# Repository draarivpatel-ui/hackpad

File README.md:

# AarivPad - My 3x3 Mechanical Macropad + EC11 Rotary Encoder + OLED

**Try the Live Interactive 3D Hardware Workbench & KMK Simulator:** [https://aariv.me/hackpad/](https://aariv.me/hackpad/)

I designed and built **AarivPad** for the Hack Club Stardance **Hackpad** mission. It is a custom 3x3 mechanical macropad powered by a **Seeed Studio XIAO RP2040**, an **Alps EC11 rotary encoder** with push-button switch, a **0.91" 128x32 SSD1306 I2C OLED status display**, and four **SK6812 MINI-E reverse-mount addressable RGB underglow LEDs**.

Alongside the complete KiCad 8 schematic, 2-layer routed PCB, JLCPCB Gerber archive, parametric OpenSCAD enclosure STLs, and CircuitPython KMK firmware, I also built an interactive browser workbench at [https://aariv.me/hackpad/](https://aariv.me/hackpad/) so you can test all 9 keys across all 3 macro layers, spin the EC11 encoder, inspect the 2-layer copper traces, and orbit the exploded 3D CAD assembly directly in your browser.

## Why I Built This

Whenever I am working across terminal Git sessions, KiCad PCB layout, and media playback, I constantly find myself reaching for awkward multi-finger keyboard chords (`git status`, `git diff --stat`, `git log --oneline -n 15`, switching tmux panes, or toggling KiCad copper layers and track widths).

I wanted a compact desk companion that sits right next to my mouse and gives me:
1. **Nine tactile mechanical switches** arranged in a standard `19.05mm` (`0.75"`) 3x3 grid for single-press macros.
2. **A physical EC11 rotary encoder** at the top-right corner so I can scrub timelines, adjust volume, or zoom in and out of KiCad/CAD viewports with tactile detents.
3. **A crisp 128x32 SSD1306 OLED screen** at the top-left so I never have to guess which macro layer (`L0: GIT/DEV`, `L1: MEDIA/RGB`, or `L2: KICAD/CAD`) is currently active.

## Features & How It Works Under the Hood

### 1. 3x3 Anti-Ghosting Switch Matrix + Peripherals on 11 GPIOs
Because the **Seeed Studio XIAO RP2040** exposes exactly 11 user GPIO pins (`D0` through `D10`), fitting 9 switches, a quadrature rotary encoder + push button, an I2C OLED display, and an addressable RGB LED chain required careful pin budgeting:
- **Columns (`COL0..COL2`)**: Wired to `D0` (`GPIO26`), `D1` (`GPIO27`), and `D2` (`GPIO28`).
- **Rows (`ROW0..ROW2`)**: Wired to `D3` (`GPIO29`), `D6` (`GPIO0`), and `D7` (`GPIO1`) through nine `1N4148W` SOD-123 switching diodes (`D1..D9`) oriented `COL2ROW` so pressing any combination of keys simultaneously never causes ghosting.
- **Hardware I2C0 (`SDA` / `SCL`)**: Reserved `D4` (`GPIO6`) and `D5` (`GPIO7`) for the 0.91" 128x32 SSD1306 OLED display at address `0x3C`.
- **EC11 Encoder & Underglow Chain**: Quadrature channels `ENC_A` and `ENC_B` connect to `D8` (`GPIO2`) and `D9` (`GPIO4`), while `D10` (`GPIO3`) handles the encoder push switch (`ENC_SW`) and drives the 4-pixel `SK6812 MINI-E` RGB underglow chain.

### 2. Three-Layer KMK Firmware (`firmware/code.py`)
I wrote the firmware in CircuitPython using **KMK** (`kmk_keyboard`, `Layers`, `EncoderHandler`, `RGB`, and `adafruit_displayio_ssd1306`):
- **Layer 0 (`GIT / TERMINAL`)**: Single-key macros for `git status -sb`, `git diff --stat`, `git add -A && git commit`, `git log --oneline -n 12`, `git pull --rebase`, `git push`, tmux pane split, terminal clear, and layer cycle (`DF(1)`). Rotary dial scrolls terminal history line by line.
- **Layer 1 (`MEDIA / RGB`)**: Play/Pause, Next/Previous Track, Mute, RGB Hue/Animation toggle, Brightness step, and Window Snap shortcuts. Rotary dial controls system volume (`VOL+` / `VOL-`).
- **Layer 2 (`KICAD / CAD`)**: KiCad track routing (`X`), via placement (`V`), copper layer flip (`F.Cu <-> B.Cu`), DRC inspector, 3D viewer launch (`Alt+3`), and measurement tool. Rotary dial zooms the canvas in and out.

### 3. 2-Layer 68mm x 84mm PCB & Parametric OpenSCAD Enclosure
- **KiCad 8 PCB (`pcb/aarivpad.kicad_pcb`)**: Routed on a compact `68.0mm x 84.0mm` two-layer board with `1.6mm` FR4 thickness, rounded `3.0mm` corners, four `M2` mounting holes (`4.0mm` inset), `0.25mm` signal traces (`0.50mm` power rails), and stitched `GND` copper pours on both `F.Cu` and `B.Cu`.
- **3D-Printable Case (`cad/aarivpad_case.scad`)**: Includes a heat-set `M2` bottom tray (`bottom_case.stl`), a `1.5mm`/`3.0mm` clip-in MX switch plate (`switch_plate.stl`) with a framed viewport over the OLED and clearance for the EC11 bushing, and a knurled `6.0mm` D-shaft knob (`encoder_knob.stl`). Total print weight is `~58g` PLA - well under the 300g Printing Legion limit.

## What Was Tricky to Build

1. **Fitting 9 Keys + OLED + EC11 + RGB onto the XIAO RP2040's 11 Pins**:
   A direct-pin wiring approach would have needed `9 (switches) + 2 (I2C) + 3 (encoder) + 1 (RGB) = 15 GPIOs`, which exceeds the XIAO RP2040's 11 pins. Scanning the 9 switches as a `3x3` diode matrix reduced the switches from 9 pins down to 6 (`3 cols + 3 rows`), leaving `D4/D5` free for hardware I2C and `D8/D9/D10` free for the EC11 encoder and RGB chain.
2. **Preventing Mechanical Interference Between the OLED Header and Top Switch Row**:
   On a tight `68mm x 84mm` board, placing the XIAO RP2040, the 0.91" OLED module, and the EC11 rotary encoder along the top header zone required carefully offsetting the OLED center to `(22.0mm, 14.5mm)` and the EC11 shaft to `(52.5mm, 14.5mm)` so the top switch row (`SW1..SW3` at `Y = 34.0mm`) clears both the OLED PCB edge and the 18mm knurled encoder knob with zero keycap rub.

## XIAO RP2040 Pinout & Matrix Wiring

| Seeed XIAO RP2040 Pin | Net Name | Connected Hardware |
| --- | --- | --- |
| `D0 / GPIO26` | `COL0` | Column 0 Switch Bus (`SW1`, `SW4`, `SW7`) |
| `D1 / GPIO27` | `COL1` | Column 1 Switch Bus (`SW2`, `SW5`, `SW8`) |
| `D2 / GPIO28` | `COL2` | Column 2 Switch Bus (`SW3`, `SW6`, `SW9`) |
| `D3 / GPIO29` | `ROW0` | Row 0 Diode Bus (`D1`, `D2`, `D3` cathodes) |
| `D6 / GPIO0` | `ROW1` | Row 1 Diode Bus (`D4`, `D5`, `D6` cathodes) |
| `D7 / GPIO1` | `ROW2` | Row 2 Diode Bus (`D7`, `D8`, `D9` cathodes) |
| `D4 / GPIO6 (SDA)` | `I2C_SDA` | 0.91" 128x32 SSD1306 OLED Display (`SDA`) |
| `D5 / GPIO7 (SCL)` | `I2C_SCL` | 0.91" 128x32 SSD1306 OLED Display (`SCL`) |
| `D8 / GPIO2` | `ENC_A` | EC11 Rotary Encoder Phase A |
| `D9 / GPIO4` | `ENC_B` | EC11 Rotary Encoder Phase B |
| `D10 / GPIO3` | `ENC_SW` | EC11 Push Switch + SK6812 RGB Underglow Chain |
| `3V3 / 5V / GND` | Power | OLED `VCC` (`3V3`), SK6812 `VDD` (`5V`), Common Ground |

## Bill of Materials (Hackpad Kit Compatible)

| Ref | Qty | Component | Footprint / Package |
| --- | --- | --- | --- |
| `U1` | 1 | Seeed Studio XIAO RP2040 | Through-hole / SMD 14-pin Module |
| `SW1-SW9` | 9 | Cherry MX / Gateron 5-Pin Mechanical Switches | `SW_Cherry_MX_1.00u_PCB` |
| `D1-D9` | 9 | 1N4148W / 1N4148 Switching Diodes | `D_SOD-123` (THT compatible pads) |
| `SW10` | 1 | Alps EC11 Rotary Encoder with Push Switch | `RotaryEncoder_Alps_EC11E-Switch` |
| `U2` | 1 | 0.91" 128x32 SSD1306 I2C OLED Display | 4-Pin 2.54mm Header (`GND/VCC/SCL/SDA`) |
| `LED1-LED4` | 4 | SK6812 MINI-E Addressable RGB LEDs | Reverse-Mount `PLCC4 3.2x2.8mm` |
| `K1-K9` | 9 | 1u Blank DSA PBT Keycaps | Standard MX Stem |
| `H1-H4` | 4 | M2x8mm Screws + M2x5mm Brass Heat-Set Inserts | 2.2mm Mounting Holes |

## Repository Structure & How to Explore It

- **Interactive Browser Workbench**: Open [https://aariv.me/hackpad/](https://aariv.me/hackpad/) (or open `index.html` locally) to test the 9-key KMK macro simulator with Web Audio mechanical switch clicks, rotate the EC11 encoder, inspect the 2-layer PCB traces (`F.Cu`, `B.Cu`, `F.SilkS`), and orbit the 3D exploded CAD assembly.
- **KiCad 8 Design Files**: Open `pcb/aarivpad.kicad_pro` in KiCad 8 to inspect the schematic (`pcb/aarivpad.kicad_sch`) and routed PCB (`pcb/aarivpad.kicad_pcb`). Fabrication-ready Gerbers are zipped at `pcb/gerbers/aarivpad-gerbers.zip`.
- **3D Enclosure CAD**: Open `cad/aarivpad_case.scad` in OpenSCAD or slice `cad/bottom_case.stl`, `cad/switch_plate.stl`, and `cad/encoder_knob.stl` directly in Bambu Studio / PrusaSlicer.
- **Firmware**: Copy `firmware/code.py` onto your XIAO RP2040's `CIRCUITPY` drive with the `kmk` and `adafruit_displayio_ssd1306` libraries installed.

## License

MIT.

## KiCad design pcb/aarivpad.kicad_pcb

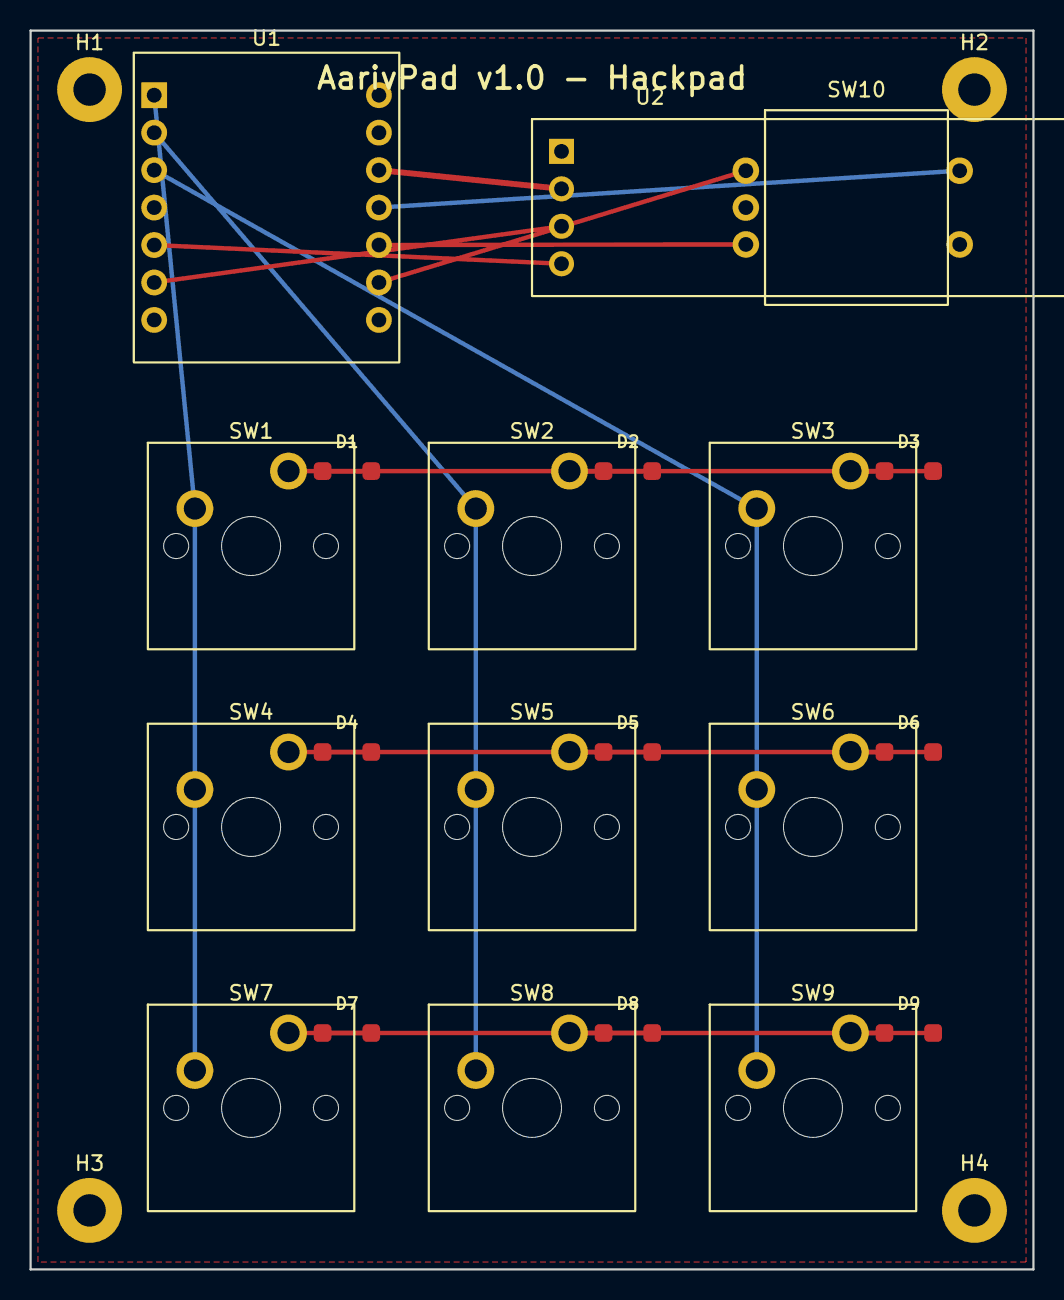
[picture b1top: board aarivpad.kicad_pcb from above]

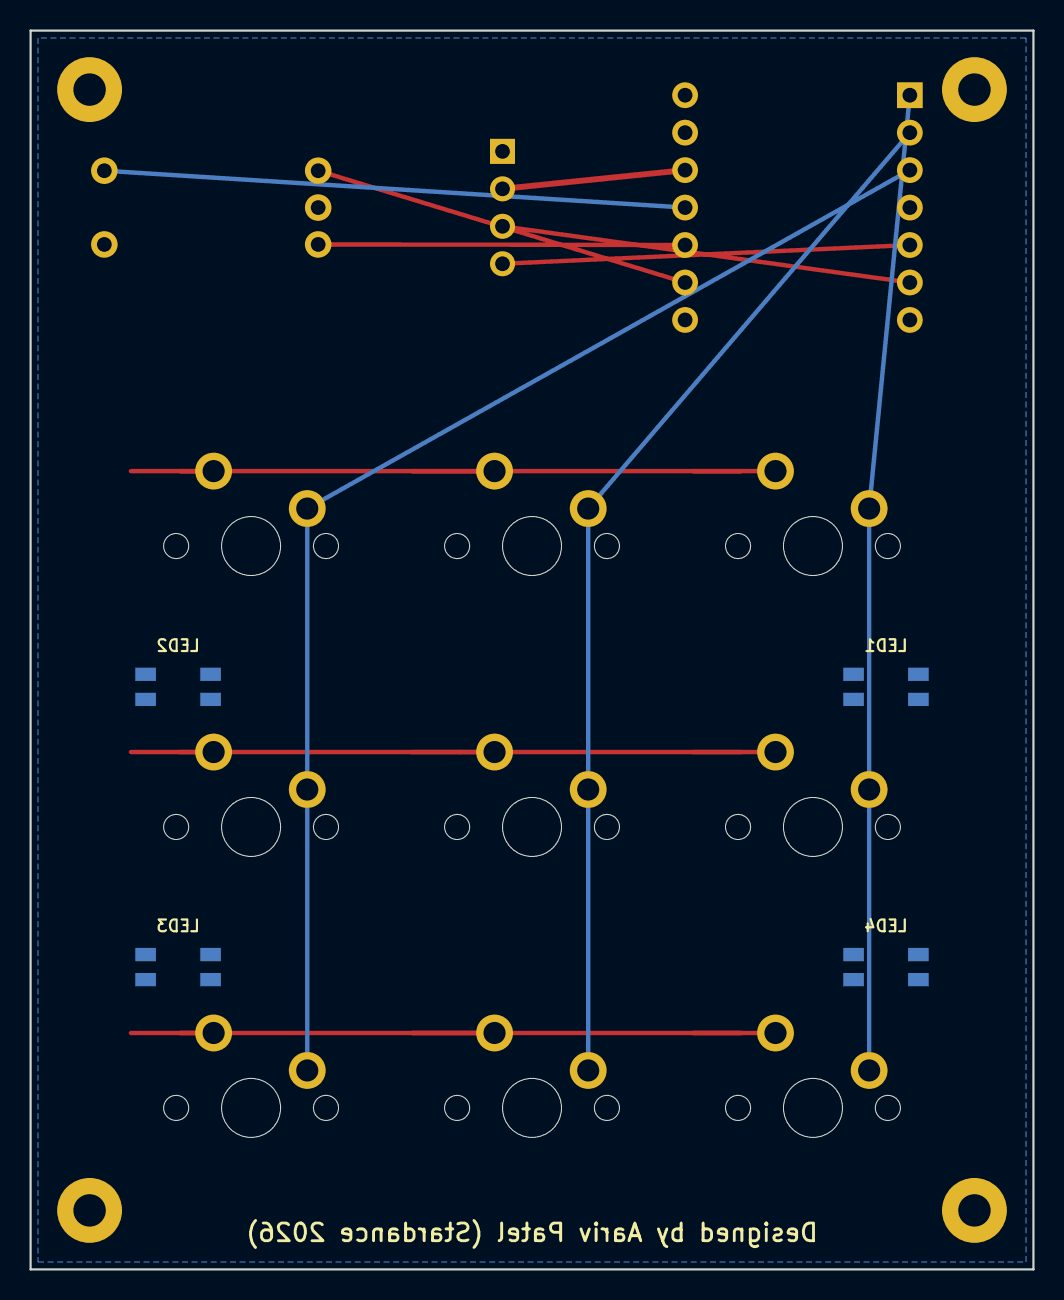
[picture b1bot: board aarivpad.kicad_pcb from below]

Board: 2 copper layers, 68.0 x 84.0 mm, 29 parts (4 on the bottom side), 26 nets.

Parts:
D1, D2, D3, D4, D5, D6, D7, D8, D9: 1N4148W; D_SOD-123
H1, H2, H3, H4: M2; MountingHole_2.2mm_M2_Pad_Via
LED1, LED2, LED3, LED4: SK6812; LED_SK6812MINI-E_PLCC4_3.2x2.8mm
SW1: MX_K1; SW_Cherry_MX_1.00u_PCB
SW2: MX_K2; SW_Cherry_MX_1.00u_PCB
SW3: MX_K3; SW_Cherry_MX_1.00u_PCB
SW4: MX_K4; SW_Cherry_MX_1.00u_PCB
SW5: MX_K5; SW_Cherry_MX_1.00u_PCB
SW6: MX_K6; SW_Cherry_MX_1.00u_PCB
SW7: MX_K7; SW_Cherry_MX_1.00u_PCB
SW8: MX_K8; SW_Cherry_MX_1.00u_PCB
SW9: MX_K9; SW_Cherry_MX_1.00u_PCB
SW10: EC11; RotaryEncoder_Alps_EC11E-Switch_Vertical_H20mm
U1: Seeed_XIAO_RP2040; Seeed_XIAO_RP2040_THT
U2: OLED_128x32; SSD1306_128x32_0.91

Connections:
+3V3: U1.12, U2.2
+5V: LED1.1, LED2.1, LED3.1, LED4.1, U1.14
COL0: SW1.1, SW4.1, SW7.1, U1.1
COL1: SW2.1, SW5.1, SW8.1, U1.2
COL2: SW3.1, SW6.1, SW9.1, U1.3
ENC_A: SW10.A, U1.9
ENC_B: SW10.B, U1.10
ENC_SW: SW10.S1, U1.11
GND: H1.1, H2.1, H3.1, H4.1, LED1.3, LED2.3, LED3.3, LED4.3, SW10.C, SW10.S2, U1.13, U2.1
I2C_SCL: U1.6, U2.3
I2C_SDA: U1.5, U2.4
LED_N1: LED1.2, LED2.4
LED_N2: LED2.2, LED3.4
LED_N3: LED3.2, LED4.4
ROW0: D1.1, D2.1, D3.1, U1.4
ROW1: D4.1, D5.1, D6.1, U1.7
ROW2: D7.1, D8.1, D9.1, U1.8
SW1_D: D1.2, SW1.2
SW2_D: D2.2, SW2.2
SW3_D: D3.2, SW3.2
SW4_D: D4.2, SW4.2
SW5_D: D5.2, SW5.2
SW6_D: D6.2, SW6.2
SW7_D: D7.2, SW7.2
SW8_D: D8.2, SW8.2
SW9_D: D9.2, SW9.2

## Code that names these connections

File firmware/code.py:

# AarivPad - 3x3 Mechanical Macropad + EC11 Rotary Encoder + 128x32 OLED + SK6812 Underglow
# Target MCU: Seeed Studio XIAO RP2040 (CircuitPython + KMK Firmware)
# Pinout matches pcb/aarivpad.kicad_pcb:
#   Columns: COL0=D0 (GPIO26), COL1=D1 (GPIO27), COL2=D2 (GPIO28)
#   Rows:    ROW0=D3 (GPIO29), ROW1=D6 (GPIO0),  ROW2=D7 (GPIO1)
#   I2C OLED (SSD1306 128x32): SDA=D4 (GPIO6), SCL=D5 (GPIO7)
#   EC11 Encoder: A=D8 (GPIO2), B=D9 (GPIO4), SW=D10 (GPIO3)
#   SK6812 RGB Underglow (4 pixels): NEOPIXEL / Status LED chain

import board
import busio
import displayio
import terminalio
from adafruit_display_text import label
import adafruit_displayio_ssd1306

from kmk.kmk_keyboard import KMKKeyboard
from kmk.keys import KC
from kmk.scanners import DiodeOrientation
from kmk.modules.layers import Layers
from kmk.modules.encoder import EncoderHandler
from kmk.extensions.media_keys import MediaKeys
from kmk.extensions.rgb import RGB, AnimationModes

keyboard = KMKKeyboard()

# Matrix configuration (3 columns x 3 rows, 1N4148W SOD-123 diodes COL2ROW)
keyboard.col_pins = (board.D0, board.D1, board.D2)
keyboard.row_pins = (board.D3, board.D6, board.D7)
keyboard.diode_orientation = DiodeOrientation.COL2ROW

# Load KMK modules & extensions
layers = Layers()
encoder_handler = EncoderHandler()
media_keys = MediaKeys()

# 4x SK6812 MINI-E Reverse-Mount Underglow LEDs
rgb = RGB(
    pixel_pin=board.NEOPIXEL,
    num_pixels=4,
    val_limit=120,
    hue_default=145,
    sat_default=255,
    val_default=90,
    animation_mode=AnimationModes.BREATHING_RAINBOW,
)

keyboard.modules = [layers, encoder_handler]
keyboard.extensions = [media_keys, rgb]

# Configure EC11 Rotary Encoder (Pin A = D8, Pin B = D9, Push Switch = D10)
encoder_handler.pins = ((board.D8, board.D9, board.D10, False),)

# Useful composite shortcuts for Git, Terminal, and CAD workflows
GIT_ST  = KC.MACRO("git status\n")
GIT_DF  = KC.MACRO("git diff --stat\n")
GIT_LG  = KC.MACRO("git log --oneline -n 8\n")
GIT_PL  = KC.MACRO("git pull --rebase\n")
GIT_CM  = KC.MACRO('git commit -m ""')
GIT_PS  = KC.MACRO("git push\n")
TMUX_SP = KC.LCTL(KC.B)
TERM_CL = KC.LCTL(KC.L)

# 3 Layers:
# Layer 0: DEV / GIT (Git status, diff, log, pull, commit, push, tmux prefix, clear, cycle layer)
# Layer 1: MEDIA / STREAM (Mute, Play/Pause, Next, Prev, Vol-, Vol+, RGB Toggle, Hue+, cycle layer)
# Layer 2: CAD / KICAD (Home view, Top view, Front view, DRC check, Route track, Add via, 3D viewer, Zoom fit, cycle layer)
keyboard.keymap = [
    # Layer 0: Git & Terminal Workflow
    [
        GIT_ST,   GIT_DF,   GIT_LG,
        GIT_PL,   GIT_CM,   GIT_PS,
        TMUX_SP,  TERM_CL,  KC.TO(1),
    ],
    # Layer 1: Media & Underglow Control
    [
        KC.MPRV,    KC.MPLY,    KC.MNXT,
        KC.VOLD,    KC.MUTE,    KC.VOLU,
        KC.RGB_TOG, KC.RGB_HUI, KC.TO(2),
    ],
    # Layer 2: KiCad & 3D CAD Navigation
    [
        KC.HOME,       KC.KP_7,       KC.KP_1,
        KC.X,          KC.V,          KC.B,
        KC.LALT(KC.N3), KC.F1,        KC.TO(0),
    ],
]

# Rotary Encoder per-layer mapping: (CCW, CW, Push)
encoder_handler.map = [
    ((KC.VOLD, KC.VOLU, KC.MUTE),),           # Layer 0: System Volume & Mute
    ((KC.RGB_VAD, KC.RGB_VAI, KC.RGB_M_BR),), # Layer 1: Underglow Brightness & Mode
    ((KC.MW_DN, KC.MW_UP, KC.MB_MMB),),       # Layer 2: CAD Canvas Zoom & Pan Click
]

# Initialize 0.91" 128x32 SSD1306 I2C OLED on D4 (SDA) and D5 (SCL)
displayio.release_displays()
OLED_NAMES = {
    0: "L0: GIT / TERM",
    1: "L1: MEDIA / RGB",
    2: "L2: KICAD / CAD",
}

try:
    i2c = busio.I2C(board.D5, board.D4)
    display_bus = displayio.I2CDisplay(i2c, device_address=0x3C)
    oled = adafruit_displayio_ssd1306.SSD1306(display_bus, width=128, height=32)

    splash = displayio.Group()
    title_lbl = label.Label(terminalio.FONT, text="AARIVPAD v1.0", color=0xFFFFFF, x=2, y=6)
    layer_lbl = label.Label(terminalio.FONT, text=OLED_NAMES[0], color=0xFFFFFF, x=2, y=18)
    status_lbl = label.Label(terminalio.FONT, text="ENC:VOL  RGB:ON", color=0xFFFFFF, x=2, y=28)
    splash.append(title_lbl)
    splash.append(layer_lbl)
    splash.append(status_lbl)
    oled.root_group = splash

    class OLEDLayerStatus(Layers):
        def after_hid_send(self, keyboard):
            super().after_hid_send(keyboard)
            active = keyboard.active_layers[0]
            layer_lbl.text = OLED_NAMES.get(active, "L0: GIT / TERM")

    keyboard.modules[0] = OLEDLayerStatus()
except Exception:
    # Allow keyboard operation even if OLED is disconnected during bench testing
    pass

if __name__ == "__main__":
    keyboard.go()
